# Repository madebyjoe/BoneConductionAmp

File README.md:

# Bone Conduction Amplifier

This is a board that was designed to interface with another 3.5mm audio out. Idealy it was to be used in conjunction with a Sena20s headset. The output goes to a stereo set of bone conduction transducers.

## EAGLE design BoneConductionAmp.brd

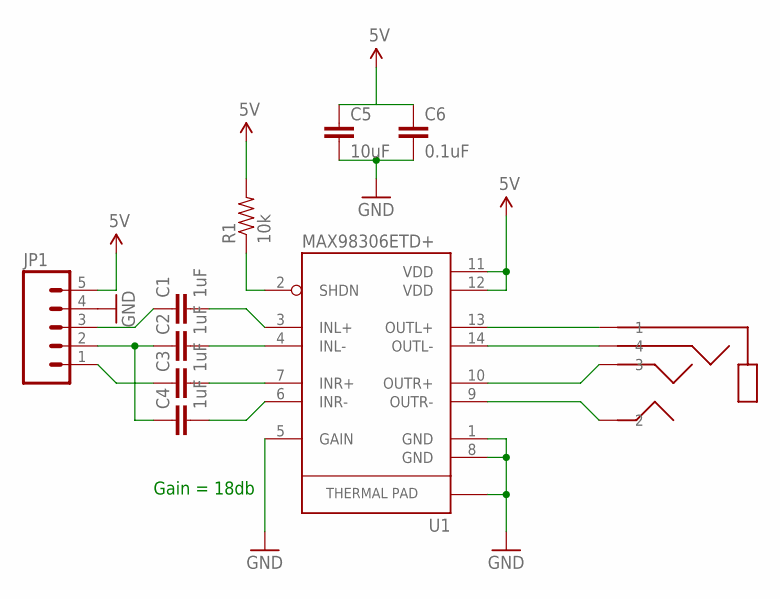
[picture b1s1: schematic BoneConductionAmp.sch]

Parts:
C1, C2, C3, C4: 1uF; 0402-CAP
C5: 10uF; 0805
C6: 0.1uF; 0402-CAP
JP1: M05PTH; 1X05
R1: 10k; 0603-RES
U1: MAX98306ETD+; 14-TDFN
U$4: TRRS-2.5MM-FEMALE4-CON; TRRS-2.5MM-JACK-SMD

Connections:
5V: C5.1, C6.1, JP1.5, R1.2, U1.11 (VDD), U1.12 (VDD)
GND: C5.2, C6.2, JP1.4, U1.1 (GND), U1.5 (GAIN), U1.8 (GND), U1.15 (GND)
unnamed: C1.2, U1.3 (INL+)
unnamed: C2.2, U1.4 (INL-)
unnamed: C3.2, U1.7 (INR+)
unnamed: C4.2, U1.6 (INR-)
unnamed: U1.9 (OUTR-), U$4.P2 (2)
unnamed: U1.10 (OUTR+), U$4.P3 (3)
unnamed: R1.1, U1.2 (SHDN)
unnamed: C1.1, JP1.3
unnamed: C2.1, C4.1, JP1.2
unnamed: C3.1, JP1.1
unnamed: U1.14 (OUTL-), U$4.P4 (4), U$4.P4.1 (4)
unnamed: U1.13 (OUTL+), U$4.P1 (1)

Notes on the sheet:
Gain = 18db

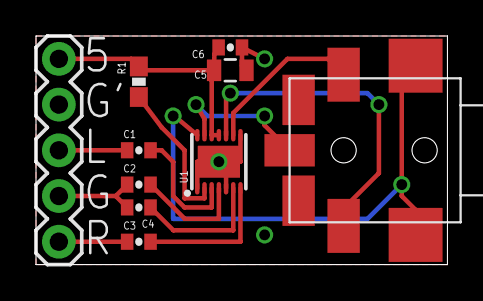
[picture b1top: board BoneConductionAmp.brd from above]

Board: 2 copper layers, 22.9 x 12.7 mm, 10 parts (0 on the bottom side), 14 nets.

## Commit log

2018-02-09 initial commit. Adds schematic and layout as well as gerbers. Complete.
2018-02-09 Created license
2018-02-09 added schematic pdf

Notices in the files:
parts and their libraries:
SparkFun-PowerIC: Licensing: CC v3.0 Share-Alike You are welcome to use this library for commercial purposes.
